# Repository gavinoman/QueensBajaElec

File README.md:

# QueensBajaElec
Repository for Queen's university Baja Electrical subteam.
Seeing if this works

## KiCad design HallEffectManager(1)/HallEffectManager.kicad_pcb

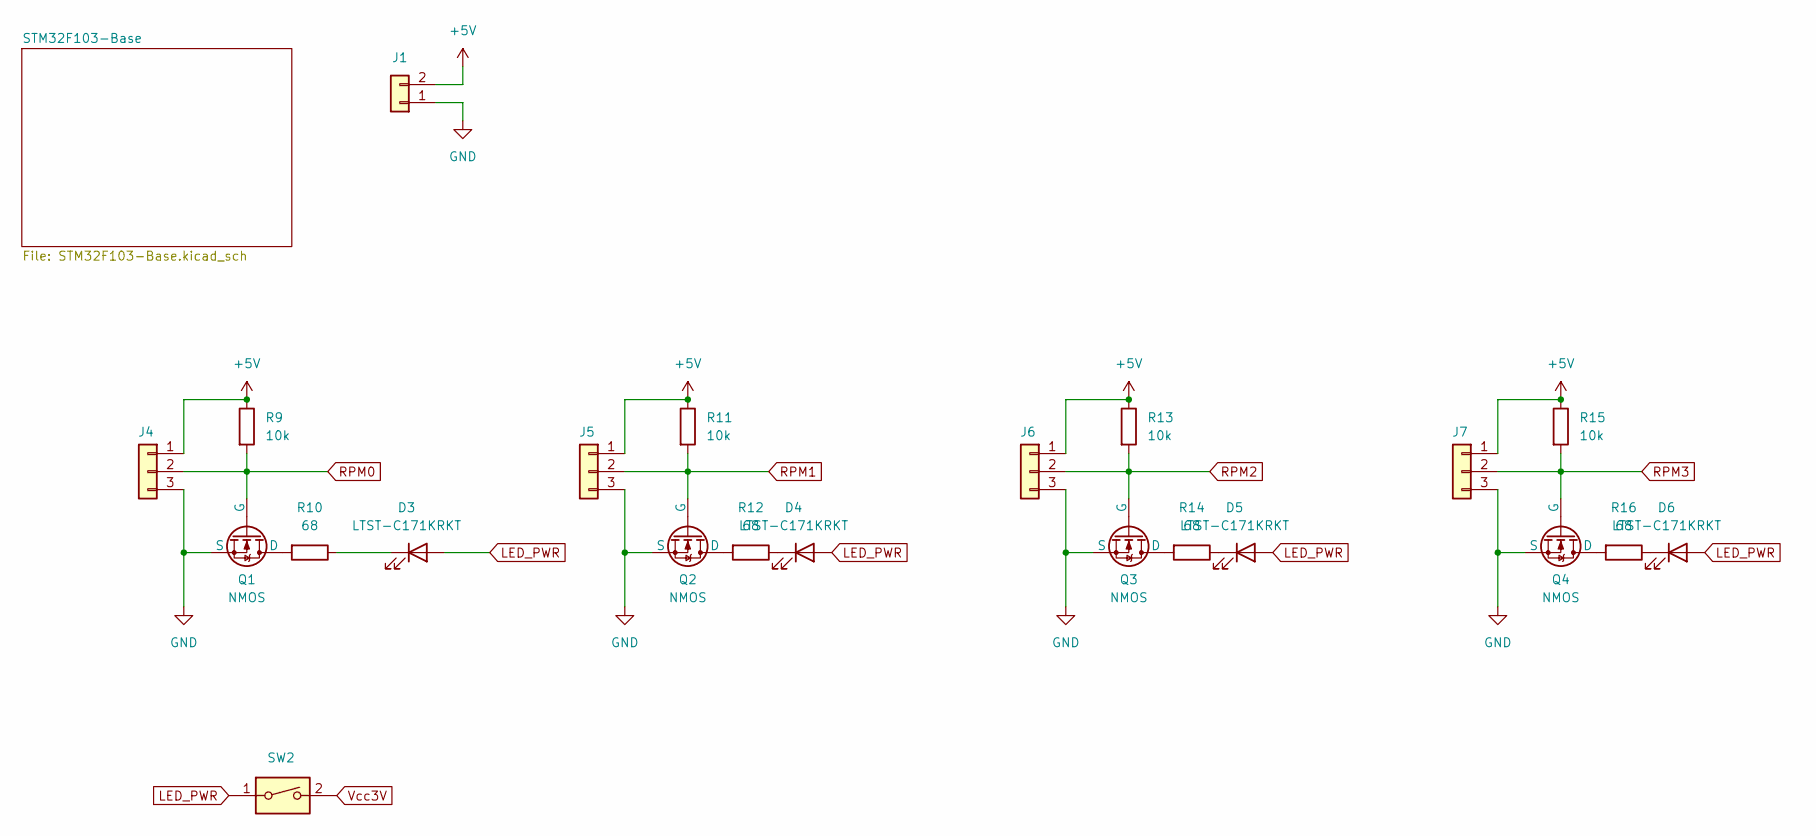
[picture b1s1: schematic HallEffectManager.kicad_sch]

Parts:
D3, D4, D5, D6: LTST-C171KRKT; LED_0805_2012Metric_Pad1.15x1.40mm_HandSolder; Digikey Part Number 160-1427-1-ND
J1: S2B-PH-K-S; CONN_S2B-PH-K-S_JST-2x1-Female; Digikey Part Number 455-1719-ND
J4, J5, J6, J7: Conn_01x03; CONN_S3B-PH-K-S_JST-3x1-Female; Digikey Part Number 455-1720-ND
Q1, Q2, Q3, Q4: NMOS; SOT-23_Handsoldering; Digikey Part Number 1727-4789-1-ND
R9, R11, R13, R15: 10k; R_0603_1608Metric_Pad0.98x0.95mm_HandSolder; Digikey Part Number 541-2817-1-ND
R10, R12, R14, R16: 68; R_0603_1608Metric_Pad0.98x0.95mm_HandSolder; Digikey Part Number 311-68.0HRCT-ND
SW2: SW_DIP_x01; CHS-01B_NDC-M; Digikey Part Number 563-1004-1-ND

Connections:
+5V: J1.2, J4.1, J5.1, J6.1, J7.1, R9.1, R11.1, R13.1, R15.1; also elsewhere on the board
GND: J1.1, J4.3, J5.3, J6.3, J7.3, Q1.3 (S), Q2.3 (S), Q3.3 (S), Q4.3 (S); also elsewhere on the board
LED_PWR: D3.2 (A), D4.2 (A), D5.2 (A), D6.2 (A), SW2.1
unnamed: D3.1 (K), R10.1
unnamed: D4.1 (K), R12.1
unnamed: D5.1 (K), R14.1
unnamed: D6.1 (K), R16.1
unnamed: Q1.1 (D), R10.2
unnamed: Q2.1 (D), R12.2
unnamed: Q3.1 (D), R14.2
unnamed: Q4.1 (D), R16.2
RPM0: J4.2, Q1.2 (G), R9.2; also elsewhere on the board
RPM1: J5.2, Q2.2 (G), R11.2; also elsewhere on the board
RPM2: J6.2, Q3.2 (G), R13.2; also elsewhere on the board
RPM3: J7.2, Q4.2 (G), R15.2; also elsewhere on the board
Vcc3V: SW2.2; also elsewhere on the board

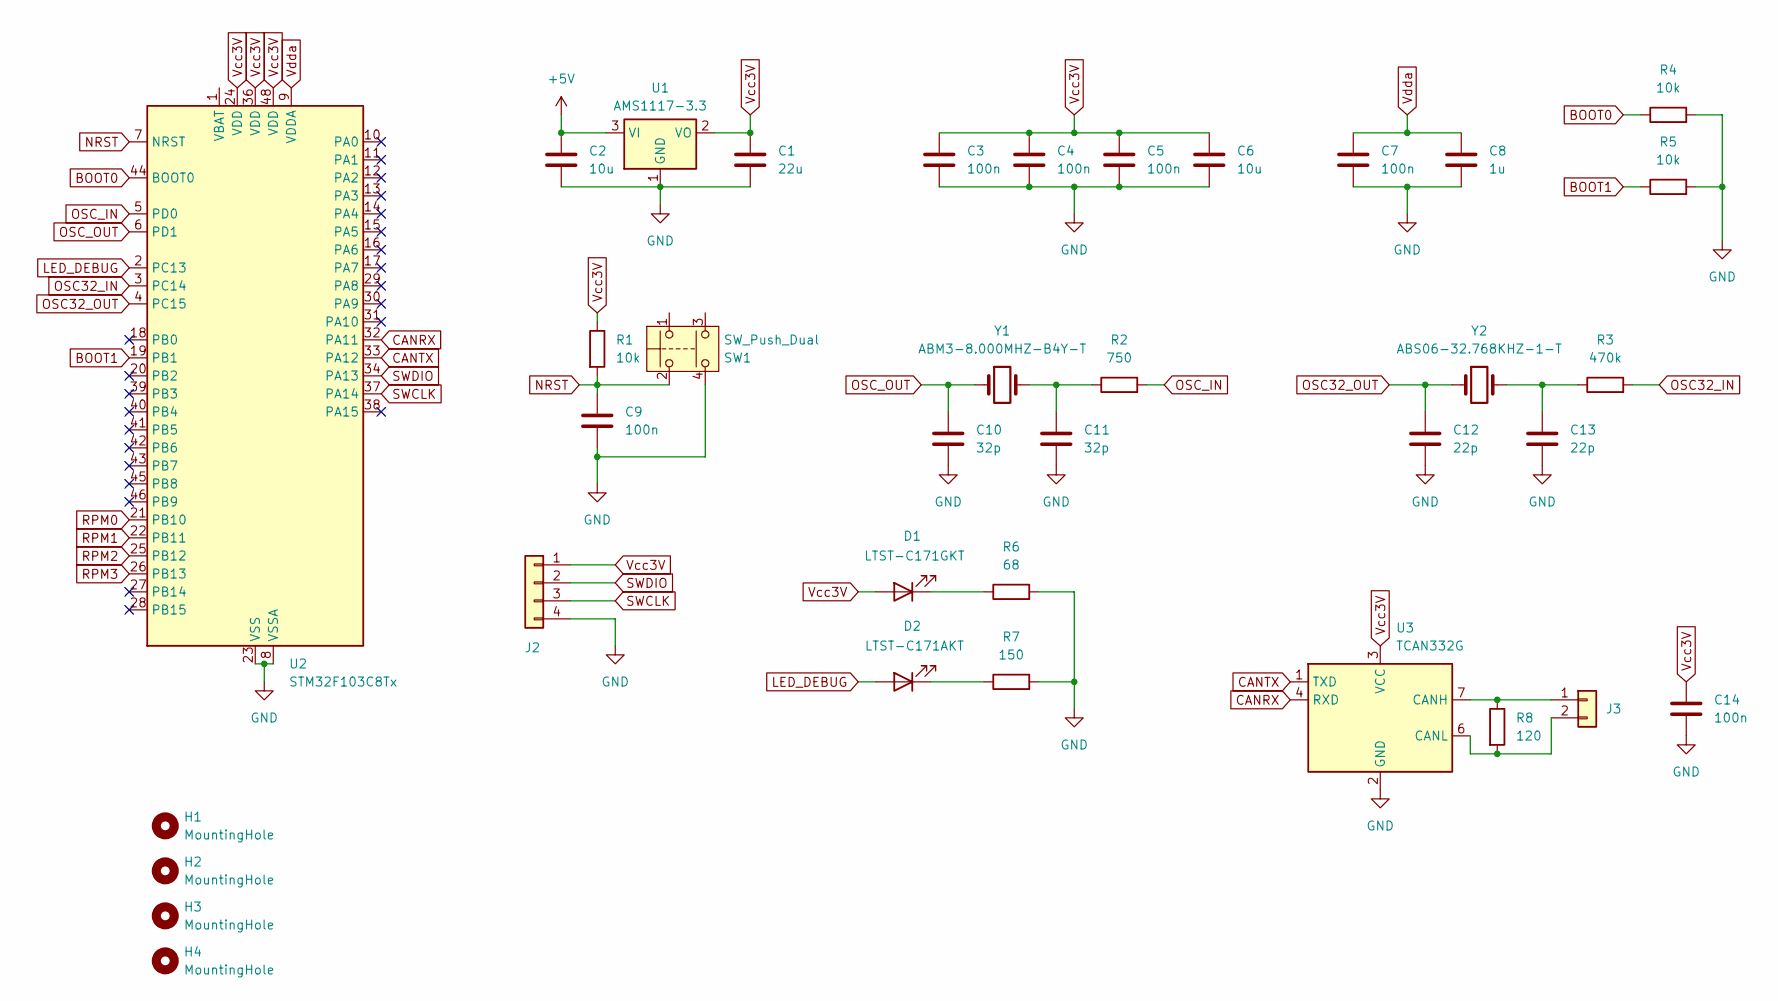
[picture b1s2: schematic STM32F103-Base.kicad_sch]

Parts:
C1: 22u; C_0603_1608Metric_Pad1.08x0.95mm_HandSolder; Digikey Part Number 490-10476-1-ND
C2, C6: 10u; C_0603_1608Metric_Pad1.08x0.95mm_HandSolder; Digikey Part Number 490-3896-1-ND
C3, C4, C5, C7, C9, C14: 100n; C_0603_1608Metric_Pad1.08x0.95mm_HandSolder; Digikey Part Number 490-3285-1-ND
C8: 1u; C_0603_1608Metric_Pad1.08x0.95mm_HandSolder; Digikey Part Number 490-1543-1-ND
C10, C11: 32p; C_0603_1608Metric_Pad1.08x0.95mm_HandSolder; Digikey Part Number 478-06031A320FAT2ACT-ND
C12, C13: 22p; C_0603_1608Metric_Pad1.08x0.95mm_HandSolder; Digikey Part Number 399-C0603C220J5GACTUCT-ND
D1: LTST-C171GKT; LED_0805_2012Metric_Pad1.15x1.40mm_HandSolder; Digikey Part Number 160-1423-1-ND
D2: LTST-C171AKT; LED_0805_2012Metric_Pad1.15x1.40mm_HandSolder; Digikey Part Number 160-1419-1-ND
H1, H2, H3, H4: MountingHole; Hole 8-32 Imperial
J2: Conn_01x04; CONN_S4B-PH-K-S_JST-4x1-Female; Digikey Part Number 455-1721-ND
J3: S2B-PH-K-S; CONN_S2B-PH-K-S_JST; Digikey Part Number 455-1719-ND
R1, R4, R5: 10k; R_0603_1608Metric_Pad0.98x0.95mm_HandSolder; Digikey Part Number 541-2817-1-ND
R2: 750; R_0603_1608Metric_Pad0.98x0.95mm_HandSolder; Digikey Part Number P750HCT-ND
R3: 470k; R_0603_1608Metric_Pad0.98x0.95mm_HandSolder; Digikey Part Number RMCF0603FT470KCT-ND
R6: 68; R_0603_1608Metric_Pad0.98x0.95mm_HandSolder; Digikey Part Number 311-68.0HRCT-ND
R7: 150; R_0603_1608Metric_Pad0.98x0.95mm_HandSolder; Digikey Part Number P150HCT-ND
R8: 120; R_0603_1608Metric_Pad0.98x0.95mm_HandSolder; Digikey Part Number RMCF0603FT120RCT-ND
SW1: SW_Push_Dual; SMT_FS; Digikey Part Number CKN12221-1-ND
U1: AMS1117-3.3; SOT-223-3_TabPin2; Digikey Part Number 5399-AMS1117-3.3SOT-223CT-ND
U2: STM32F103C8Tx; LQFP-48_7x7mm_P0.5mm; Digikey Part Number 497-6063-ND
U3: TCAN332G; TCAN332; Digikey Part Number 296-47355-1-ND
Y1: ABM3-8.000MHZ-B4Y-T; Crystal_SMD_5032-2Pin_5.0x3.2mm_HandSoldering; Digikey Part Number 535-13567-1-ND
Y2: ABS06-32.768KHZ-1-T; Crystal_SMD_2012-2Pin_2.0x1.2mm_HandSoldering; Digikey Part Number 535-10248-1-ND

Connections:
+5V: C2.1, U1.3 (VI); also elsewhere on the board
BOOT0: R4.1, U2.44 (BOOT0)
BOOT1: R5.1, U2.19 (PB1)
CANRX: U2.32 (PA11), U3.4 (RXD)
CANTX: U2.33 (PA12), U3.1 (TXD)
GND: C1.2, C2.2, C3.2, C4.2, C5.2, C6.2, C7.2, C8.2, C9.2, C10.2, C11.2, C12.2, C13.2, C14.1, J2.4, R4.2, R5.2, R6.2, R7.2, SW1.4, U1.1 (GND), U2.8 (VSSA), U2.23 (VSS), U2.35 (VSS), U2.47 (VSS), U3.2 (GND); also elsewhere on the board
LED_DEBUG: D2.2 (A), U2.2 (PC13)
NRST: C9.1, R1.2, SW1.2, U2.7 (NRST)
unnamed: C11.1, R2.1, Y1.2
unnamed: C13.1, R3.1, Y2.2
unnamed: D1.1 (K), R6.1
unnamed: D2.1 (K), R7.1
unnamed: J3.1, R8.1, U3.7 (CANH)
unnamed: J3.2, R8.2, U3.6 (CANL)
OSC32_IN: R3.2, U2.3 (PC14)
OSC32_OUT: C12.1, U2.4 (PC15), Y2.1
OSC_IN: R2.2, U2.5 (PD0)
OSC_OUT: C10.1, U2.6 (PD1), Y1.1
RPM0: U2.21 (PB10); also elsewhere on the board
RPM1: U2.22 (PB11); also elsewhere on the board
RPM2: U2.25 (PB12); also elsewhere on the board
RPM3: U2.26 (PB13); also elsewhere on the board
SWCLK: J2.3, U2.37 (PA14)
SWDIO: J2.2, U2.34 (PA13)
Vcc3V: C1.1, C3.1, C4.1, C5.1, C6.1, C14.2, D1.2 (A), J2.1, R1.1, U1.2 (VO), U2.24 (VDD), U2.36 (VDD), U2.48 (VDD), U3.3 (VCC); also elsewhere on the board
Vdda: C7.1, C8.1, U2.9 (VDDA)

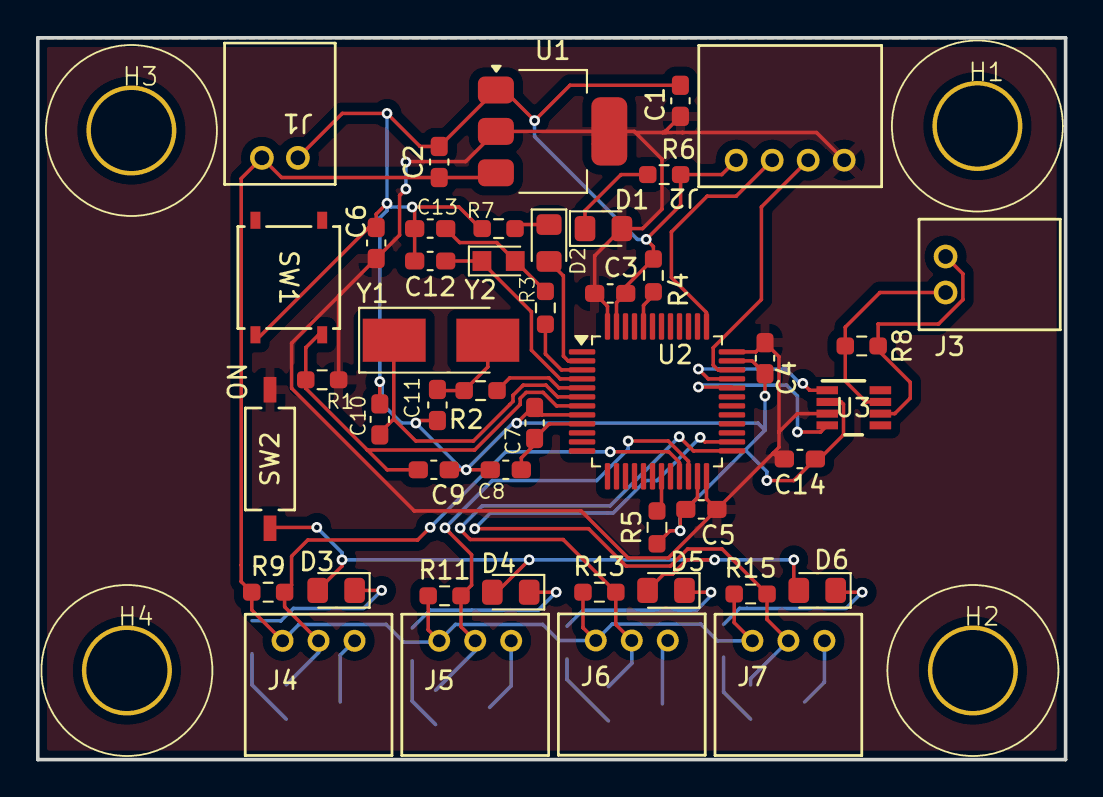
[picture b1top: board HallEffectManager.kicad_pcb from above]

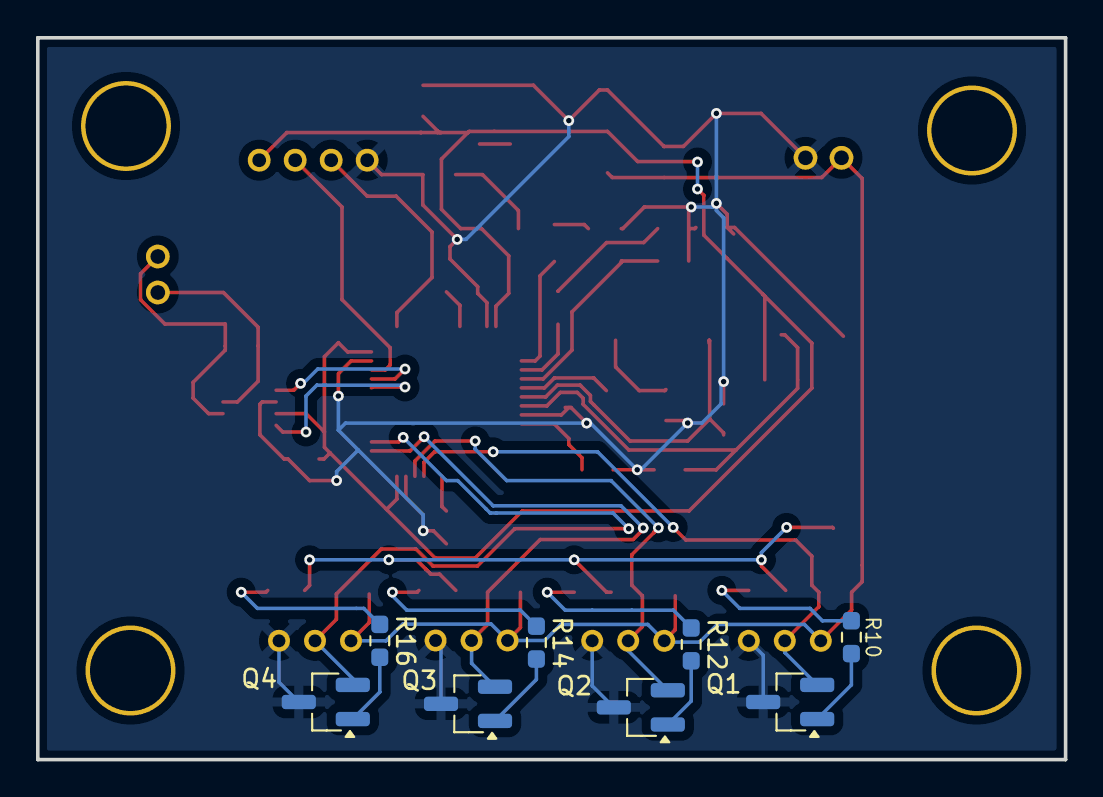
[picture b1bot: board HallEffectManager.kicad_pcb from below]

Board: 2 copper layers, 57.1 x 40.1 mm, 58 parts (8 on the bottom side), 35 nets.
